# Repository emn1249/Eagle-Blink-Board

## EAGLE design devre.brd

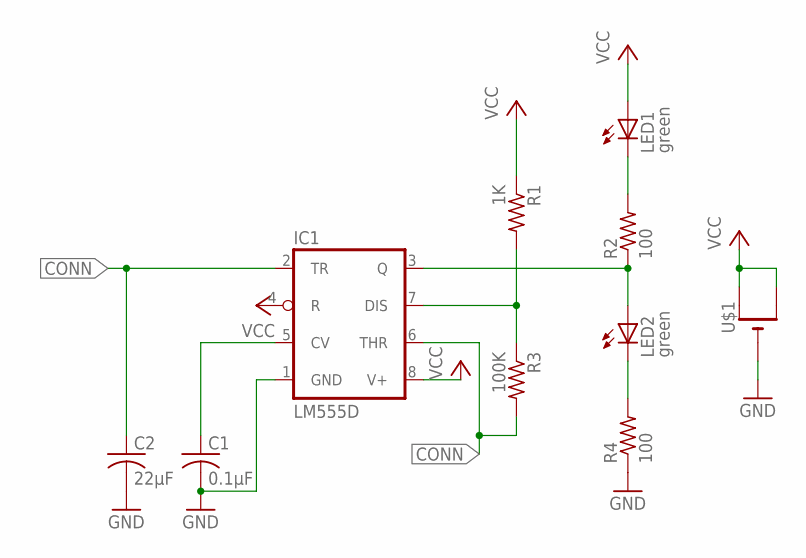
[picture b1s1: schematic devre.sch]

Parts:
C1: 0.1µF; C0805
C2: 22µF; C0805
IC1: LM555D; SO08
LED1, LED2: green; CHIP-LED0805
R1: 1K; R0805
R2, R4: 100; R0805
R3: 100K; R0805
U$1: CR1220SMT; CR1220-SMD

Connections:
CONN: C2.1, IC1.2 (TR), IC1.6 (THR), R3.2
GND: C1.2, C2.2, IC1.1 (GND), R4.1, U$1.-
unnamed: C1.1, IC1.5 (CV)
unnamed: IC1.7 (DIS), R1.2, R3.1
unnamed: LED1.C, R2.2
unnamed: IC1.3 (Q), LED2.A, R2.1
unnamed: LED2.C, R4.2
VCC: IC1.4 (R), IC1.8 (V+), LED1.A, R1.1, U$1.+$1 (+), U$1.+$2 (+1)

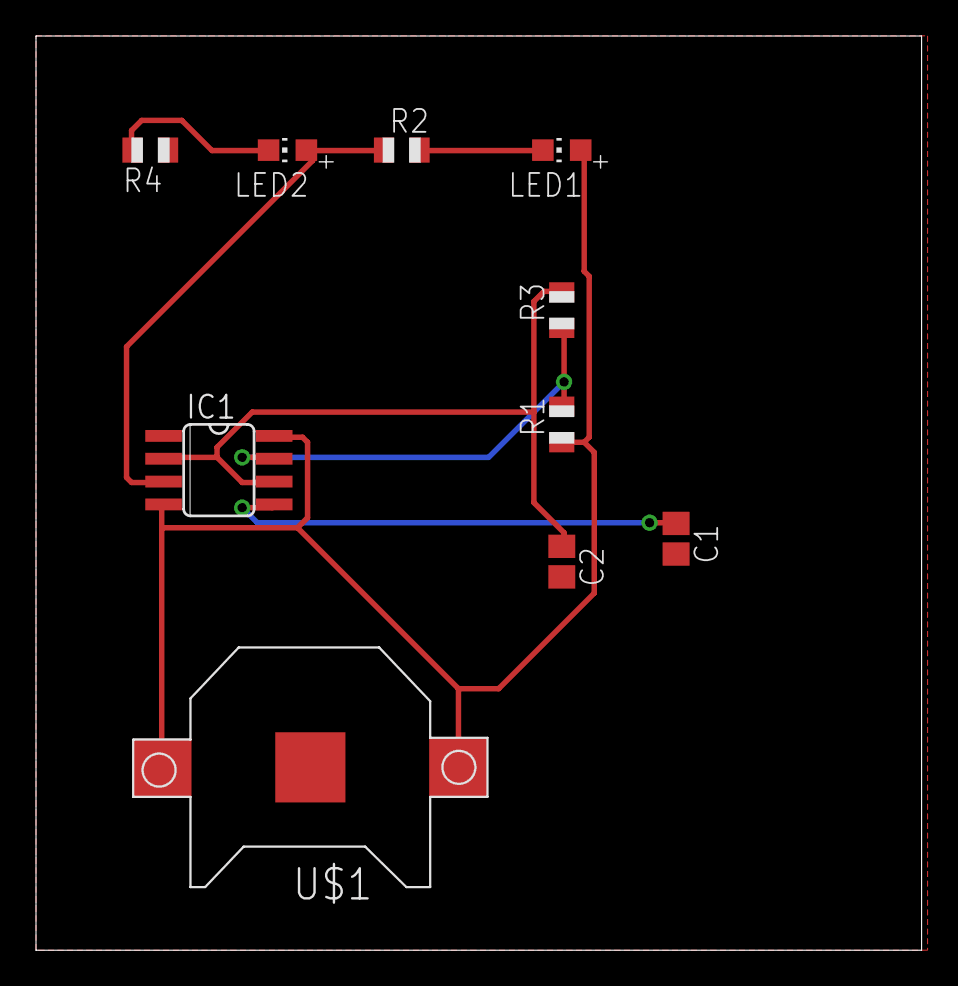
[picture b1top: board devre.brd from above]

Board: 2 copper layers, 49.2 x 50.8 mm, 10 parts (0 on the bottom side), 8 nets.

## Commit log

2020-06-22 Eagle-Blinky Board
